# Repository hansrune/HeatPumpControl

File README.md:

# Generic ESP32 C3/C6 board with IR blaster, serial port, i2c, 1-wire and more

A small DYI generic mini IO based on ESP32C3 or ESP32C6 from Xiaomi SeeedStudio. This board has an IR blaster, IR receiver, and serial port with a simple 5V - 3.3V level shifter suitable for Mitsubishi CN105 port (similar for any RS-232 interfaces) . Other ESP32 pins are available with pin headers for I2C, 1-wire, and other general purposes

This board is tested with ESPhome and ESPEasy [firmware](#firmwares) (build instructions below), and is easily used with home automation systems that support MQTT auto discovery, the native Home Assistant API, and the many [controllers that ESPEasy supports](https://espeasy.readthedocs.io/en/latest/Controller/_Controller.html)

A [3D printed box](#./FreeCAD/) STL files and  the FreeCAD design is also available

**PLEASE NOTE**: Use at your own risk. The ESPhome firmwares are unofficial and reverse-engineered Mitsubishi protocol based on the [Swicago library](https://github.com/SwiCago/HeatPump). The authors and contributors have extensively tested this firmware. Please note that not all units support every feature. If you need an officially supported method to remotely control your Mitsubishi device via WiFi, a commercial solution is available [here](https://www.mitsubishi-electric.co.nz/wifi/)

## Introduction

This small IO board was made to easily fit inside a small DYI box, a heat pump or other.

For Mitsubushi heat pumps, the CN105 connector is used for serial port communications and for power supply.

Some of the main features and benefits

- **Serial port with simple level shifter for 5V serial ports**
    - The CN105 port of Mitsubishi ports can be used - and will then also provide the power supply for the board
- **An IR blaster circuit**
    - Some features / command packets are easier to find from a native IR receiver
- **I2C and/or 1-wire**
- **Other GPIO ports**
- **WiFi based**
    - This is almost a must have for most home automation systems
    - OTA support
    - Configuration backup, restore and bulk updates.
- **Firmware of your choise**
    - ESPEasy with Domoticz over http. Device creation uses virtual sensors
    - ESPEasy with Domoticz and Home Assistant via MQTT. Device creation uses a MQTT configuration text file.
    - ESPHome to Home Assistant via MQTT and auto discovery
    - ESPHome to Domoticz via MQTT and auto discovery
    - ... and as the hardware supports using both Arduino and ESP-IF development kits, almost any other firmware can be created.
- **3D printed enclosure**
    - [FreeCAD](./FreeCAD) and `.stl` files provided
- **Seed Studio XIAO ESP32C3**
    - This device is well shielded and comes with an externam IPX antenna connector
    - FCC and CE regulations approved

### Heat pump wiring

The wiring for a Mistubishi heat pump:

A visible LED can be used in series with the IR LED - just in case you want to see the activity

The serial port - CN105 - on our Mitsubishi heat pumps:

The IR sender led fits inside the receiver housing:

And the device including enclosure is tiny, i.e. easy to find room for inside the heat pump:

### Wiring for other purposes

The same PCB can be used for many other purposes. Here is for a firmware build test with CO2 sensor, I2C temp/humid and light, PIR sensor and a 1-wire temp sensor

## Implementation and design

The schematic diagram is [available here](KiCad/HeatPumpControl-schema-2.0.pdf). The [KiCad EDA](https://www.kicad.org/) project is in the [same folder](./KiCad)

## GPIO pin usage

| PIN      | Capabilty          | Function                            |
|----------|--------------------|-------------------------------------|
| GPIO2    | Pulled up          | N/A                                 |
| GPIO3/A1 | Generic IO         | On IR receiver pin header           |
| GPIO4    | Actice high out    | IR sender                           |
| GPIO5    | Generic IO         | Pull-up possible                    |
| GPIO6    | I2C                | SDA                                 |
| GPIO7    | I2C                | SCL                                 |
| GPIO9    | Active low out     | Internal status LED                 |
| GPIO10   | Generic IO         | Pull-up possible                    |
| GPIO20   | RX                 | Serial to heatpump TX               |
| GPIO21   | TX                 | Serial to heatpump RX               |

## Hardware - getting started

This project uses my [KiCad-lib-ESP32 repository](https://github.com/hansrune/KiCad-lib-ESP32.git) as a [git submodule](https://www.git-scm.com/book/en/v2/Git-Tools-Submodules). To check this out, use the following:

```bash
git clone --recurse-submodules https://github.com/hansrune/HeatPumpControl.git 
```

### Materials used

This project uses the [Seed Studio XIAO ESP32C3 RISC-V module](https://www.seeedstudio.com/Seeed-XIAO-ESP32C3-p-5431.html). This tiny device has proven to be more reliable than most ESP8266 modules. This module also comes with an IPX connector for an external antenna, and is delivered with a simple external antenna for good range.

5V power can be supplied over USB-C or the serial port pin headers

For more information, use [this KiCad BOM](KiCad/HeatPumpControl-BOM.csv)

## Hardware assembly

Soldering a prototype by hand is possible if you have a steady hand and a small solder iron tip. A microscope is recommended to propely inspect the solder joints.

Recommend to do the SMD parts first, then other components.

## 3D printed enclosure

An enclosure made in [FreeCAD](https://www.freecad.org/) is available in [this folder](./FreeCAD). You may also just use the `.stl` files for your 3D printer slicer.

## Firmwares

### ESPHome

ESPHome firmware can be set up from [this ESPHome configuration repository](https://github.com/hansrune/esphome-config) using the `test_mitsubishi_hp.yaml` as a template

Follow the [README](https://github.com/hansrune/esphome-config) for instruction on what you will likely want to change.

By default, both the serial CN105 interface as well as the IR sender is set up in this firmware. You likely want just one of them.

In Home Assistant, there is this serial port / CN105 connected control

The IR blaster control:

<p align="center">
    
</p

And the diagnostics / device details:

No 1-wire and lux sensor connected in this case

### ESPEasy

ESPEasy can be used with a number of different controllers / home automation systms. A custom firmware build description is [available here](https://github.com/hansrune/ESPEasy-custom/blob/builds/custom/mega-20240822-1/README-custombuilds.md)

ESPEasy requires many settings. For configuration settings and rule files, you can upload the files from [this page](./ESPEasy/) as a starting point. Please make sure to change name, unit number, controller IP addresses, NTP, syslog host and latitude/longitude. This configuration uses both a MQTT controller and a Domoticz controller. Change to what you need.

### Alternatve firmware

You may be interested in looking at alternative firmwares such as [this one](https://github.com/echavet/MitsubishiCN105ESPHome)

## Known bugs

The version 2.0 PCB has some flaws that fairly easy to work around:

- The NPN-tranistor need to be mounted upside down
- The copper fill grounding is missing for the IR receiver GND pin. An added wire is needed if you use it

## License

This project is licensed under the [GNU General Public License v3.0](GNU-LICENSE-V3.txt) for the software, [CERN-OHL-W](OHL-LICENSE.txt) for the hardware, and [CC BY-SA](CC-BY-SA-LICENCE.txt) for the documentation and ideas.

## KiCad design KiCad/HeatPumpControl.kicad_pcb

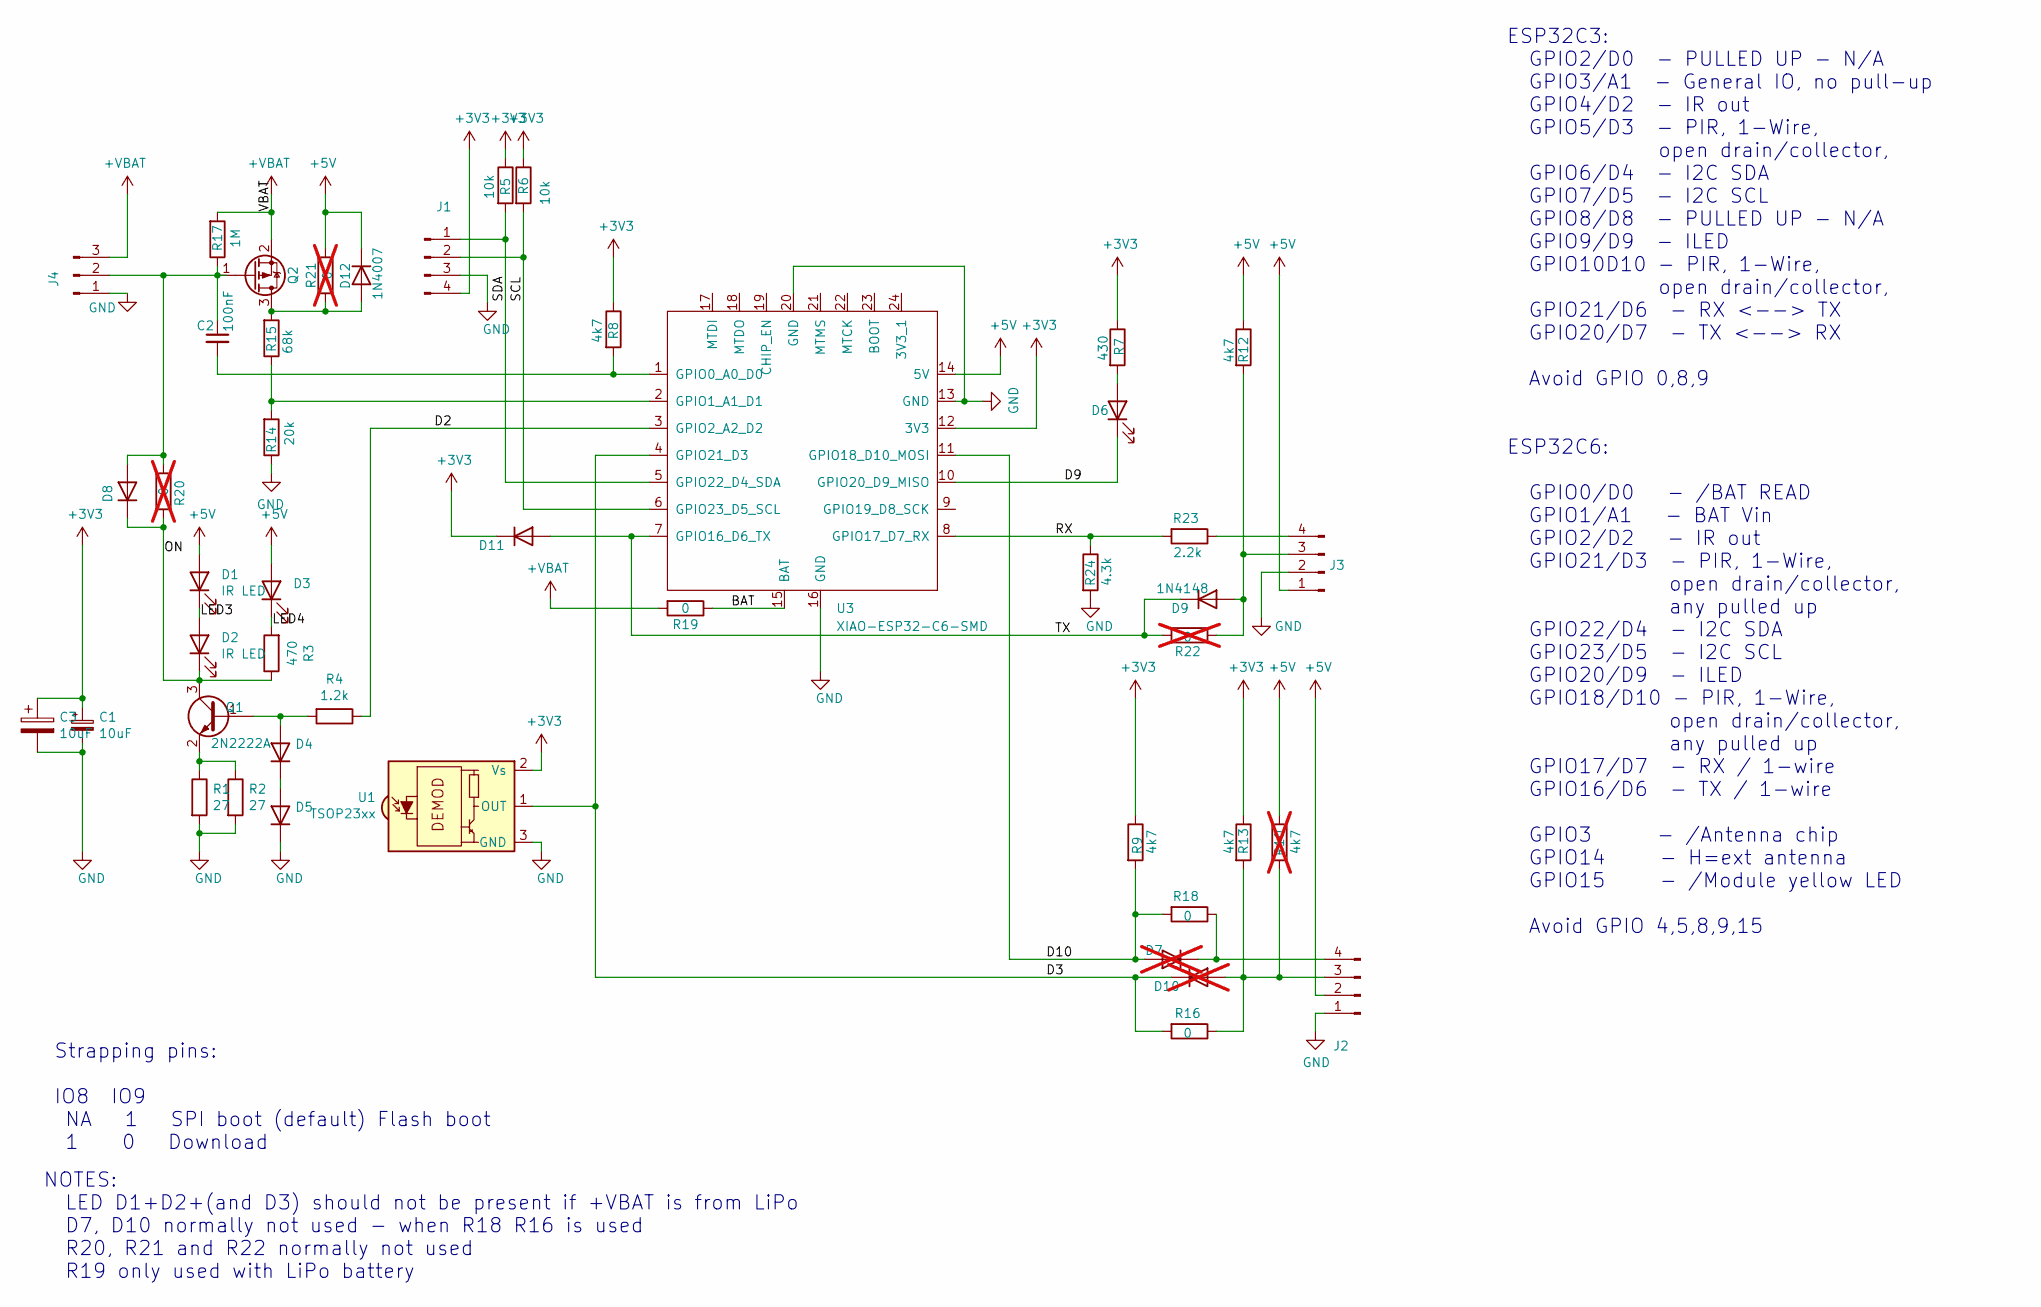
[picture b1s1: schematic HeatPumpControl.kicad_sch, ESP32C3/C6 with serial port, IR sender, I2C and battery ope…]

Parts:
C1: 10uF; CP_Radial_D5.0mm_P2.50mm
C2: 100nF; C_0805_2012Metric_Pad1.18x1.45mm_HandSolder
C3: 10uF; C_1206_3216Metric_Pad1.33x1.80mm_HandSolder
D1, D2: IR LED; LED_D5.0mm_Clear
D3, D6: LED_0805_2012Metric
D4, D5, D8, D11: 1N4148; D_SOD-323
D7: 1N4148; D_SOD-323; not fitted
D9: 1N4148; D_MiniMELF
D10: 1N4148; D_MiniMELF; not fitted
D12: 1N4007; D_SOD-123
J1, J2, J3: Conn_01x04_Male; PinHeader_1x04_P2.54mm_Vertical
J4: Conn_01x03_Male; PinHeader_1x03_P2.54mm_Vertical
Q1: 2N2222A; SOT-23_Handsoldering
Q2: Q_PMOS_GDS; SOT-23_Handsoldering
R1, R2: 27; R_0805_2012Metric
R3: 470; R_0805_2012Metric
R4: 1.2k; R_0805_2012Metric
R5, R6: 10k; R_0805_2012Metric
R7: 430; R_0805_2012Metric
R8, R9, R12, R13: 4k7; R_0805_2012Metric
R10: 4k7; R_0805_2012Metric; not fitted
R14: 20k; R_0805_2012Metric_Pad1.20x1.40mm_HandSolder
R15: 68k; R_0805_2012Metric_Pad1.20x1.40mm_HandSolder
R16, R18, R19: 0; R_0805_2012Metric
R17: 1M; R_0805_2012Metric_Pad1.20x1.40mm_HandSolder
R20, R21, R22: 0; R_0805_2012Metric; not fitted
R23: 2.2k; R_0805_2012Metric
R24: 4.3k; R_0805_2012Metric
U1: TSOP23xx; Vishay_MOLD-3Pin
U3: XIAO-ESP32-C6-SMD; XIAO-ESP32-C3C6-SMD

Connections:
+3V3: C1.1, C3.1, D11.1 (K), J1.4, R5.1, R6.1, R7.1, R8.1, R9.1, R13.1, U1.2 (Vs), U3.12 (3V3)
+5V: D1.2 (A), D3.2 (A), D12.1 (K), J2.2, J3.1, R10.1, R12.1, R21.1, U3.14 (5V)
+VBAT: J4.3, Q2.2 (S), R17.2, R19.2
/BAT: R19.1, U3.15 (BAT)
/D2: R4.1, U3.3 (GPIO2_A2_D2)
/D3: D10.1 (K), R16.2, U1.1 (OUT), U3.4 (GPIO21_D3)
/D9: D6.1 (K), U3.10 (GPIO20_D9_MISO)
/D10: D7.2 (A), R9.2, R18.2, U3.11 (GPIO18_D10_MOSI)
/LED3: D1.1 (K), D2.2 (A)
/LED4: D3.1 (K), R3.2
/ON: D2.1 (K), D8.1 (K), Q1.3 (C), R3.1, R20.2
/RX: R23.2, R24.1, U3.8 (GPIO17_D7_RX)
/SCL: J1.2, R6.2, U3.6 (GPIO23_D5_SCL)
/SDA: J1.1, R5.2, U3.5 (GPIO22_D4_SDA)
/TX: D9.1 (K), D11.2 (A), R22.2, U3.7 (GPIO16_D6_TX)
GND: C1.2, C3.2, D5.1 (K), J1.3, J2.1, J3.2, J4.1, R1.2, R2.2, R14.1, R24.2, U1.3 (GND), U3.13 (GND), U3.16 (GND), U3.20 (GND)
unnamed: D4.2 (A), Q1.1 (B), R4.2
unnamed: D4.1 (K), D5.2 (A)
unnamed: D6.2 (A), R7.2
unnamed: D7.1 (K), J2.4, R18.1
unnamed: C2.1, D8.2 (A), J4.2, Q2.1 (G), R17.1, R20.1
unnamed: D9.2 (A), J3.3, R12.2, R22.1
unnamed: D10.2 (A), J2.3, R10.2, R13.2, R16.1
unnamed: D12.2 (A), Q2.3 (D), R15.2, R21.2
unnamed: J3.4, R23.1
unnamed: Q1.2 (E), R1.1, R2.1
unnamed: C2.2, R8.2, U3.1 (GPIO0_A0_D0)
unnamed: R14.2, R15.1, U3.2 (GPIO1_A1_D1)

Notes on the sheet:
Strapping pins: IO8 IO9 NA 1 SPI boot (default) Flash boot 1 0 Download
NOTES: LED D1+D2+(and D3) should not be present if +VBAT is from LiPo D7, D10 normally not used - when R18 R16 is used R20, R21 and R22 normally not used R19 only used with LiPo battery
ESP32C3: GPIO2/D0 - PULLED UP - N/A GPIO3/A1 - General IO, no pull-up GPIO4/D2 - IR out GPIO5/D3 - PIR, 1-Wire, open drain/collector, GPIO6/D4 - I2C SDA GPIO7/D5 - I2C SCL GPIO8/D8 - PULLED UP - N/A GPIO9/D9 - ILED GPIO10D10 - PIR, 1-Wire, open drain/collector, GPIO21/D6 - RX <--> TX GPIO20/D7 - TX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

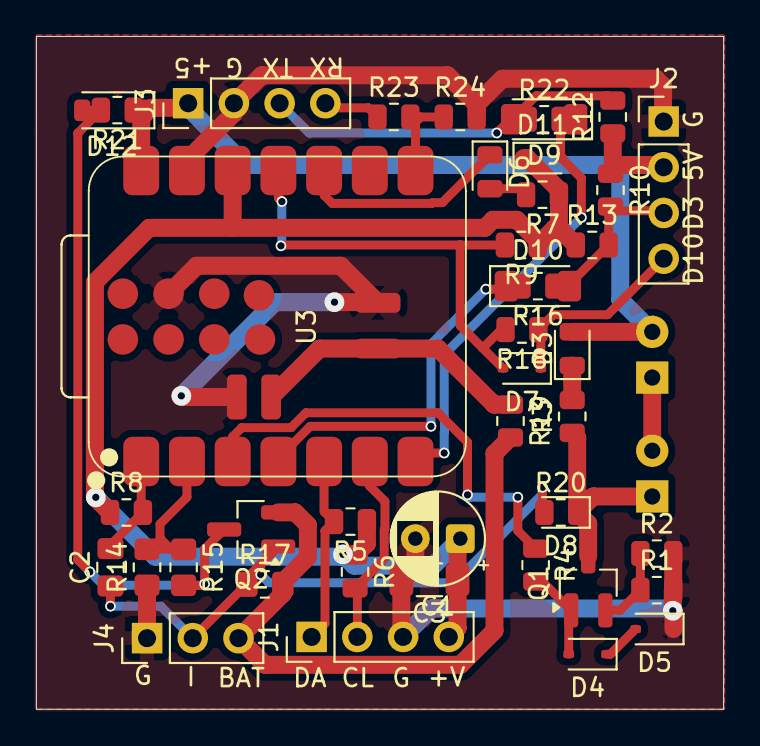
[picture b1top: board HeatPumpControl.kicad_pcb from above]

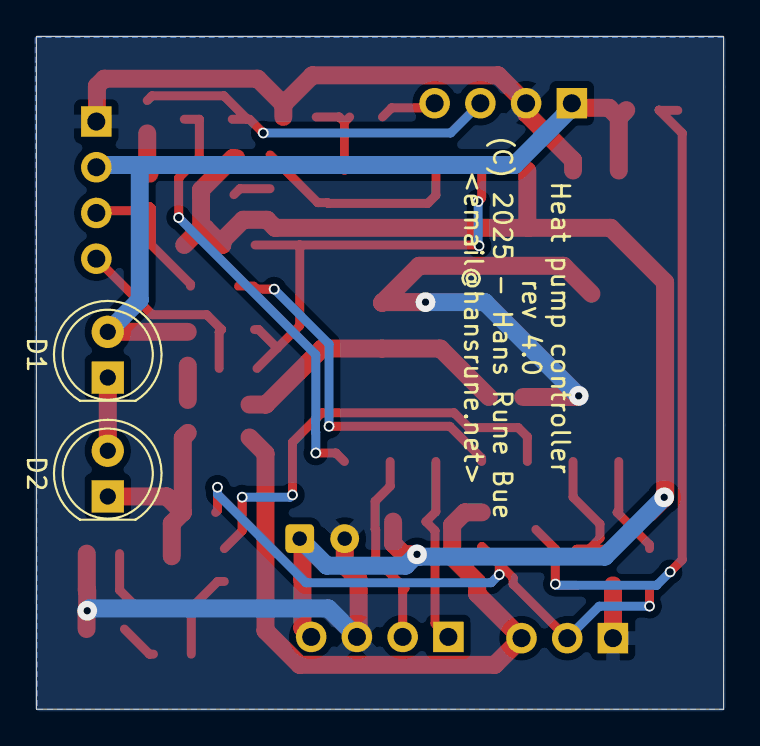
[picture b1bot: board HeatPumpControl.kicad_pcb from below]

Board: 2 copper layers, 38.2 x 37.4 mm, 45 parts (2 on the bottom side), 28 nets.

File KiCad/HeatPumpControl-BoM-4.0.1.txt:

Reference | Value | Datasheet | Footprint | Qty | DNP 
 C1  C3 | 10uF | ~ | Capacitor_SMD:C_1206_3216Metric_Pad1.33x1.80mm_HandSolder,Capacitor_THT:CP_Radial_D5.0mm_P2.50mm | 2 |  
 C2 | 100nF | ~ | Capacitor_SMD:C_0805_2012Metric_Pad1.18x1.45mm_HandSolder | 1 |  
 D1  D2 | IR  LED | ~ | LED_THT:LED_D5.0mm_Clear | 2 |  
 D3  D6 | ~ | ~ | LED_SMD:LED_0805_2012Metric | 2 |  
 D4  D5  D8  D9  D11 | 1N4148 | http://www.nxp.com/documents/data_sheet/1N4148_1N4448.pdf | Diode_SMD:D_MiniMELF,Diode_SMD:D_SOD-323 | 5 |  
 D7  D10 | 1N4148 | http://www.nxp.com/documents/data_sheet/1N4148_1N4448.pdf | Diode_SMD:D_MiniMELF,Diode_SMD:D_SOD-323 | 2 | DNP 
 J1  J2  J3 | Conn_01x04_Male | ~ | Connector_PinHeader_2.54mm:PinHeader_1x04_P2.54mm_Vertical | 3 |  
 J4 | Conn_01x03_Male | ~ | Connector_PinHeader_2.54mm:PinHeader_1x03_P2.54mm_Vertical | 1 |  
 Q1 | 2N2222A | ~ | Package_TO_SOT_SMD:SOT-23_Handsoldering | 1 |  
 Q2 | Q_PMOS_GDS | https://www.infineon.com/dgdl/irlml6402pbf.pdf?fileId=5546d4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 | Package_TO_SOT_SMD:SOT-23_Handsoldering | 1 |  
 R1  R2 | 27 | ~ | Resistor_SMD:R_0805_2012Metric | 2 |  
 R3 | 470 | ~ | Resistor_SMD:R_0805_2012Metric | 1 |  
 R4 | 1.2k | ~ | Resistor_SMD:R_0805_2012Metric | 1 |  
 R5  R6 | 10k | ~ | Resistor_SMD:R_0805_2012Metric | 2 |  
 R7 | 430 | ~ | Resistor_SMD:R_0805_2012Metric | 1 |  
 R8  R9  R12  R13 | 4k7 | ~ | Resistor_SMD:R_0805_2012Metric | 4 |  
 R10 | 4k7 | ~ | Resistor_SMD:R_0805_2012Metric | 1 | DNP 
 R14 | 20k | ~ | Resistor_SMD:R_0805_2012Metric_Pad1.20x1.40mm_HandSolder | 1 |  
 R15 | 68k | ~ | Resistor_SMD:R_0805_2012Metric_Pad1.20x1.40mm_HandSolder | 1 |  
 R16  R18  R19  R21 | 0 | ~ | Resistor_SMD:R_0805_2012Metric | 4 |  
 R17 | 1M | ~ | Resistor_SMD:R_0805_2012Metric_Pad1.20x1.40mm_HandSolder | 1 |  
 R20  R22 | 0 | ~ | Resistor_SMD:R_0805_2012Metric | 2 | DNP 
 R23 | 2.2k | ~ | Resistor_SMD:R_0805_2012Metric | 1 |  
 R24 | 4.3k | ~ | Resistor_SMD:R_0805_2012Metric | 1 |  
 U3 | XIAO-ESP32-C6-SMD |  | LOCAL1:XIAO-ESP32-C3C6-SMD | 1 |

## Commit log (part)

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2024-06-20 Initial commits
2024-06-20 Renamed pdf print files
2024-06-20 Added images
2024-06-20 Main README updates
2024-06-20 Main README updates + image
2024-06-20 Fixed Q1 pinout and grounding fills
2024-06-21 Updated Elecrow rename script
2024-06-21 New pdf prints
2024-06-21 v2.0.1 KiCAD changes
2024-06-23 README updates
2024-09-03 ESPHome and ESPEasy firmwares added
2024-09-03 3D printer enclosure added
2024-09-03 FCC and CE compliance
2024-09-03 Screenshots and images
2024-09-04 Added images from HA
2024-09-04 Images did not render in github
2024-09-04 More image corrections
2024-09-04 Image sizes adjusted
2024-09-04 more doc updates
2024-09-04 Add controller support description
2024-09-04 Add note on 3D enclosure
2024-09-12 Comment update
2024-09-17 Add notes on alternatives
2024-09-19 New 3D model
2025-03-24 Add LICENSE overview file
2025-10-15 ESP32C6 support
2025-10-20 Diode foorptint changes
2025-10-21 Add 5-3.3 V divider for Rx
2025-10-26 Added combined C3/C6 module footprint
2025-10-28 Add pdf files for v4.0
2025-10-28 Manufacturing for v4.0
2025-12-01 Add GPIO descriptions and other texts
2025-12-04 Add diode for VBAT -> 5V
2025-12-08 Readme updates for v4
2025-12-23 Change to SOD-123 for 1N4007
2025-12-25 Prints, Gerber and BOM for v4.0.3
2025-12-25 Gerber zip file renamed
2025-12-25 Missing Gerber file
2026-01-05 Fill zones updated

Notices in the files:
KiCad/HeatPumpControl.kicad_pcb:
(C) 2025 - Hans Rune Bue
KiCad/HeatPumpControl.kicad_sch:
Hardware is licensed under CERN-OHL-W-2.0
Project documents are licensed under CC-BY-SA 2.0
